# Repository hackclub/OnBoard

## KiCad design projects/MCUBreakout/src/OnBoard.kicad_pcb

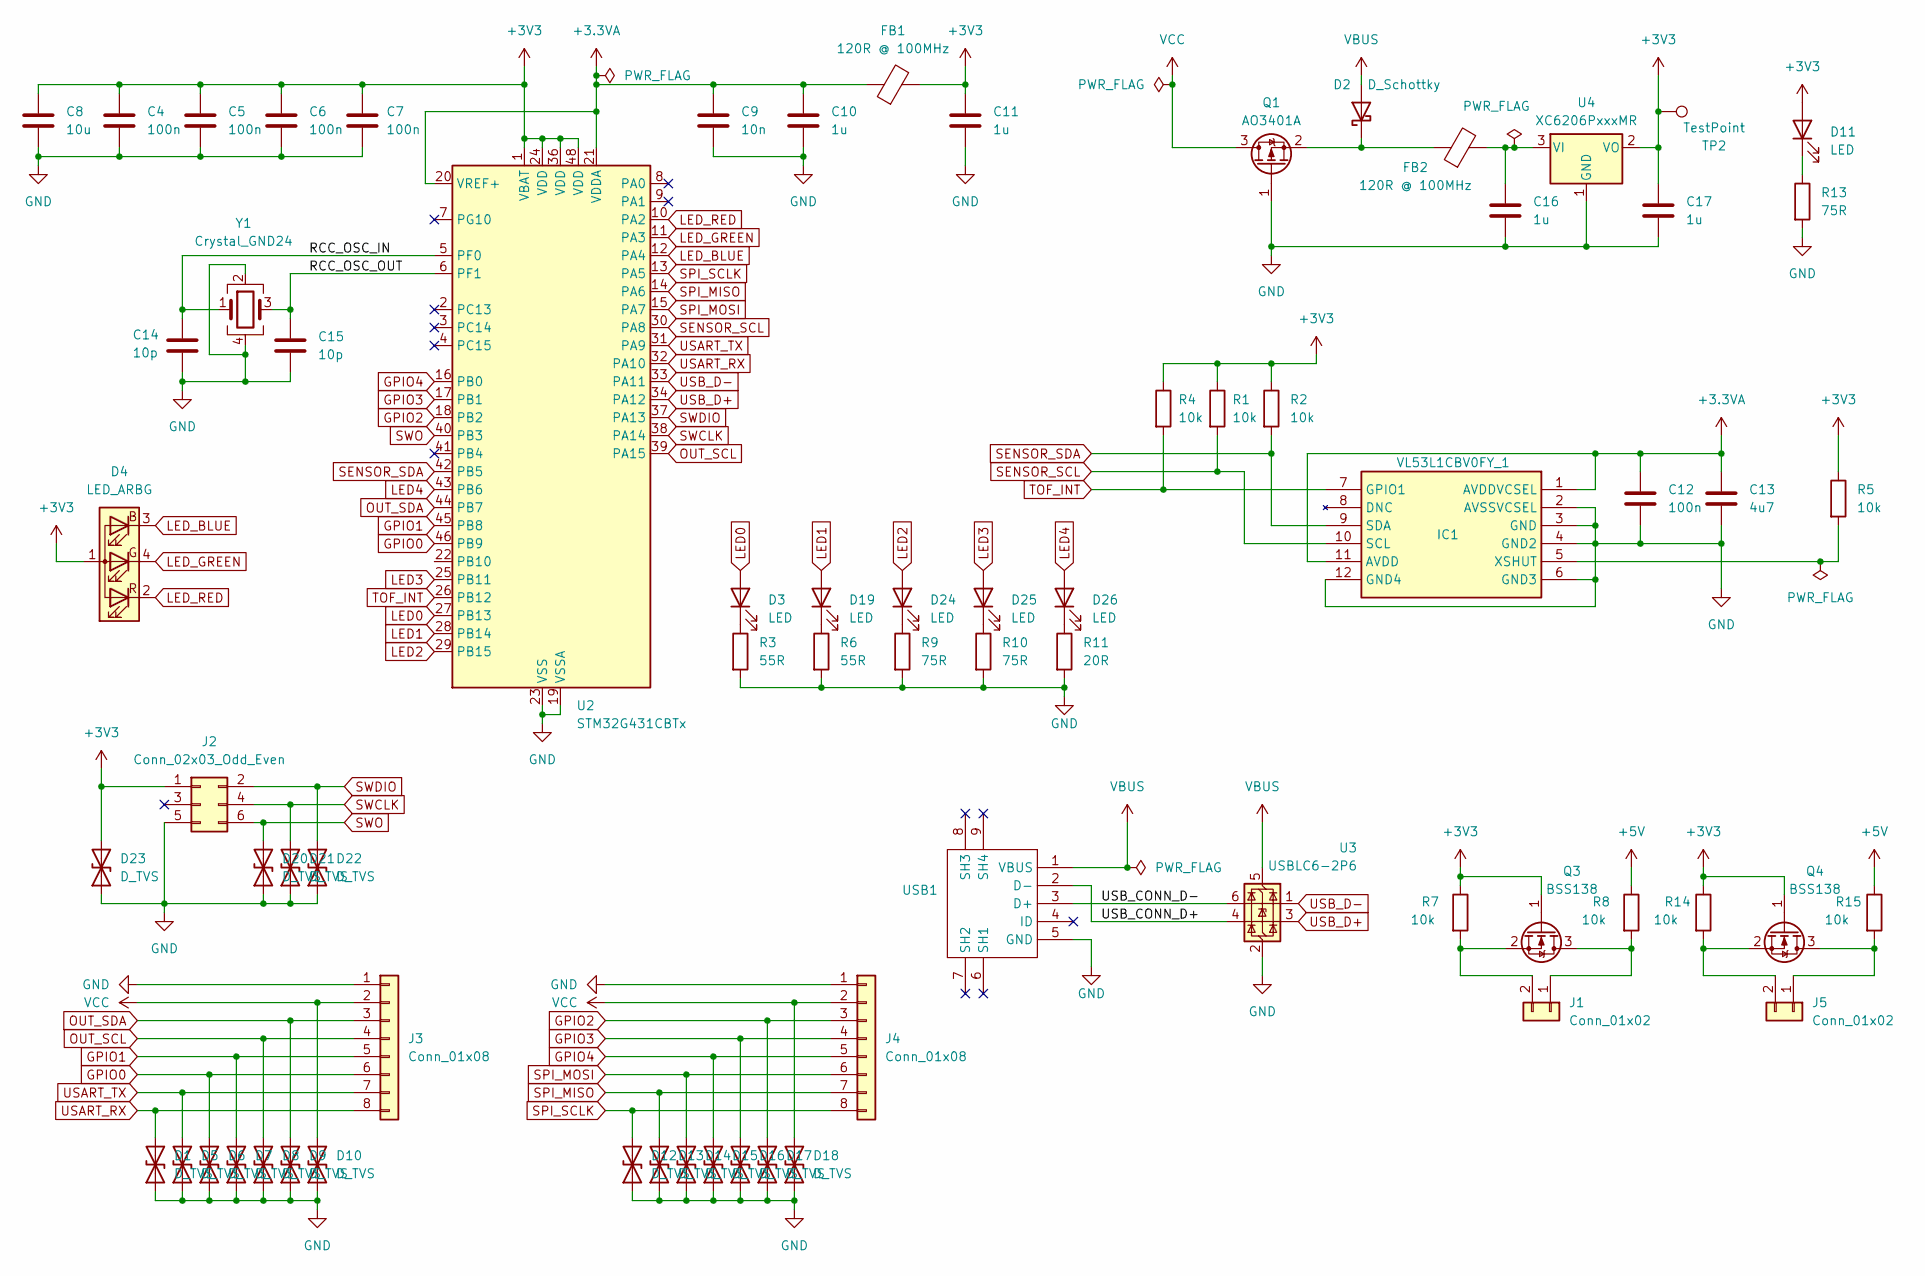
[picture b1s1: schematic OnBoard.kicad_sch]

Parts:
C4, C5, C6, C7, C12: 100n; C_0402_1005Metric
C8: 10u; C_0402_1005Metric
C9: 10n; C_0402_1005Metric
C10, C11, C16, C17: 1u; C_0402_1005Metric
C13: 4u7; C_0402_1005Metric
C14, C15: 10p; C_0402_1005Metric
D1, D5, D6, D7, D8, D9, D12, D13, D14, D15, D16, D17, D20, D21, D22, D23: D_TVS; TVS-3V3-DFN0603-2_L0.6-W0.3-BI
D2: D_Schottky; D_SOD-123
D3, D11, D19, D24, D25: LED; LED_0603_1608Metric
D4: LED_ARBG; HSMFC116
D10, D18: D_TVS; TVS-5V-DFN1006-2L-BI
D26: LED; LED_0805_2012Metric
FB1, FB2: 120R @ 100MHz; L_0603_1608Metric
IC1: VL53L1CBV0FY_1; VL53L1CBV0FY1; Manufacturer_Part_Number VL53L1CBV0FY/1; Mouser Part Number 511-VL53L1CBV0FY/1
J1, J5: Conn_01x02; PinHeader_1x02_P2.54mm_Vertical
J2: Conn_02x03_Odd_Even; Tag-Connect_TC2030-IDC-NL_2x03_P1.27mm_Vertical
J3, J4: Conn_01x08; PinHeader_1x08_P2.54mm_Vertical
Q1: AO3401A; SOT-23
Q3, Q4: BSS138; SOT-23
R1, R2, R4, R5, R7, R8, R14, R15: 10k; R_0402_1005Metric
R3, R6: 55R; R_0402_1005Metric
R9, R10, R13: 75R; R_0402_1005Metric
R11: 20R; R_0402_1005Metric
TP2: TestPoint; TestPoint_Pad_1.0x1.0mm
U2: STM32G431CBTx; LQFP-48_7x7mm_P0.5mm
U3: USBLC6-2P6; SOT-666
U4: XC6206PxxxMR; SOT-23-3
USB1: MICRO-USB-SMD_MICROXNJ; Manufacturer Part MicroXNJ; LCSC Part Name Micro-B 母 卧贴
Y1: Crystal_GND24; Crystal_SMD_3225-4Pin_3.2x2.5mm

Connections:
+3.3VA: C9.1, C10.1, C12.1, C13.1, FB1.1, IC1.1 (AVDDVCSEL), IC1.11 (AVDD), U2.20 (VREF+), U2.21 (VDDA)
+3V3: C4.1, C5.1, C6.1, C7.1, C8.1, C11.1, C17.1, D4.1 (A), D11.2 (A), D23.2 (A2), FB1.2, J2.1, Q3.1 (G), Q4.1 (G), R1.1, R2.1, R4.1, R5.1, R7.1, R14.1, TP2.1, U2.1 (VBAT), U2.24 (VDD), U2.36 (VDD), U2.48 (VDD), U4.2 (VO)
+5V: R8.1, R15.1
/RCC_OSC_IN: C14.1, U2.5 (PF0), Y1.1
/RCC_OSC_OUT: C15.1, U2.6 (PF1), Y1.3
/USB_CONN_D+: U3.4 (I/O2), USB1.2 (D-)
/USB_CONN_D-: U3.6 (I/O1), USB1.3 (D+)
GND: C4.2, C5.2, C6.2, C7.2, C8.2, C9.2, C10.2, C11.2, C12.2, C13.2, C14.2, C15.2, C16.2, C17.2, D1.1 (A1), D5.1 (A1), D6.1 (A1), D7.1 (A1), D8.1 (A1), D9.1 (A1), D10.1 (A1), D12.1 (A1), D13.1 (A1), D14.1 (A1), D15.1 (A1), D16.1 (A1), D17.1 (A1), D18.1 (A1), D20.1 (A1), D21.1 (A1), D22.1 (A1), D23.1 (A1), IC1.2 (AVSSVCSEL), IC1.3 (GND), IC1.4 (GND2), IC1.6 (GND3), IC1.12 (GND4), J2.5, J3.1, J4.1, Q1.1 (G), R3.2, R6.2, R9.2, R10.2, R11.2, R13.2, U2.19 (VSSA), U2.23 (VSS), U2.35 (VSS), U2.47 (VSS), U3.2 (GND), U4.1 (GND), USB1.5 (GND), Y1.2, Y1.4
GPIO0: D6.2 (A2), J3.6, U2.46 (PB9)
GPIO1: D7.2 (A2), J3.5, U2.45 (PB8)
GPIO2: D17.2 (A2), J4.3, U2.18 (PB2)
GPIO3: D16.2 (A2), J4.4, U2.17 (PB1)
GPIO4: D15.2 (A2), J4.5, U2.16 (PB0)
LED0: D3.2 (A), U2.27 (PB13)
LED1: D19.2 (A), U2.28 (PB14)
LED2: D24.2 (A), U2.29 (PB15)
LED3: D25.2 (A), U2.25 (PB11)
LED4: D26.2 (A), U2.43 (PB6)
LED_BLUE: D4.3 (BK), U2.12 (PA4)
LED_GREEN: D4.4 (GK), U2.11 (PA3)
LED_RED: D4.2 (RK), U2.10 (PA2)
unnamed: D2.1 (K), FB2.1, Q1.2 (S)
unnamed: D3.1 (K), R3.1
unnamed: D11.1 (K), R13.1
unnamed: D19.1 (K), R6.1
unnamed: D24.1 (K), R9.1
unnamed: D25.1 (K), R10.1
unnamed: D26.1 (K), R11.1
unnamed: IC1.5 (XSHUT), R5.2
unnamed: J1.1, Q3.3 (D), R8.2
unnamed: J1.2, Q3.2 (S), R7.2
unnamed: J5.1, Q4.3 (D), R15.2
unnamed: J5.2, Q4.2 (S), R14.2
unnamed: C16.1, FB2.2, U4.3 (VI)
OUT_SCL: D8.2 (A2), J3.4, U2.39 (PA15)
OUT_SDA: D9.2 (A2), J3.3, U2.44 (PB7)
SENSOR_SCL: IC1.10 (SCL), R1.2, U2.30 (PA8)
SENSOR_SDA: IC1.9 (SDA), R2.2, U2.42 (PB5)
SPI_MISO: D13.2 (A2), J4.7, U2.14 (PA6)
SPI_MOSI: D14.2 (A2), J4.6, U2.15 (PA7)
SPI_SCLK: D12.2 (A2), J4.8, U2.13 (PA5)
SWCLK: D21.2 (A2), J2.4, U2.38 (PA14)
SWDIO: D22.2 (A2), J2.2, U2.37 (PA13)
SWO: D20.2 (A2), J2.6, U2.40 (PB3)
TOF_INT: IC1.7 (GPIO1), R4.2, U2.26 (PB12)
USART_RX: D1.2 (A2), J3.8, U2.32 (PA10)
USART_TX: D5.2 (A2), J3.7, U2.31 (PA9)
USB_D+: U2.34 (PA12), U3.3 (I/O2)
USB_D-: U2.33 (PA11), U3.1 (I/O1)
VBUS: D2.2 (A), U3.5 (VBUS), USB1.1 (VBUS)
VCC: D10.2 (A2), D18.2 (A2), J3.2, J4.2, Q1.3 (D)

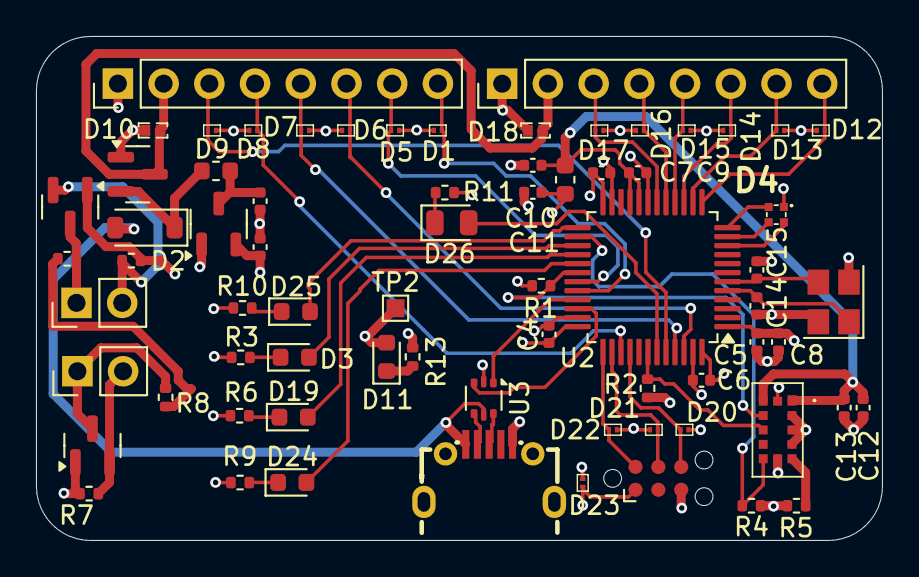
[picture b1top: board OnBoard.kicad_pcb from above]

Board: 4 copper layers, 47.0 x 28.0 mm, 71 parts (0 on the bottom side), 51 nets.

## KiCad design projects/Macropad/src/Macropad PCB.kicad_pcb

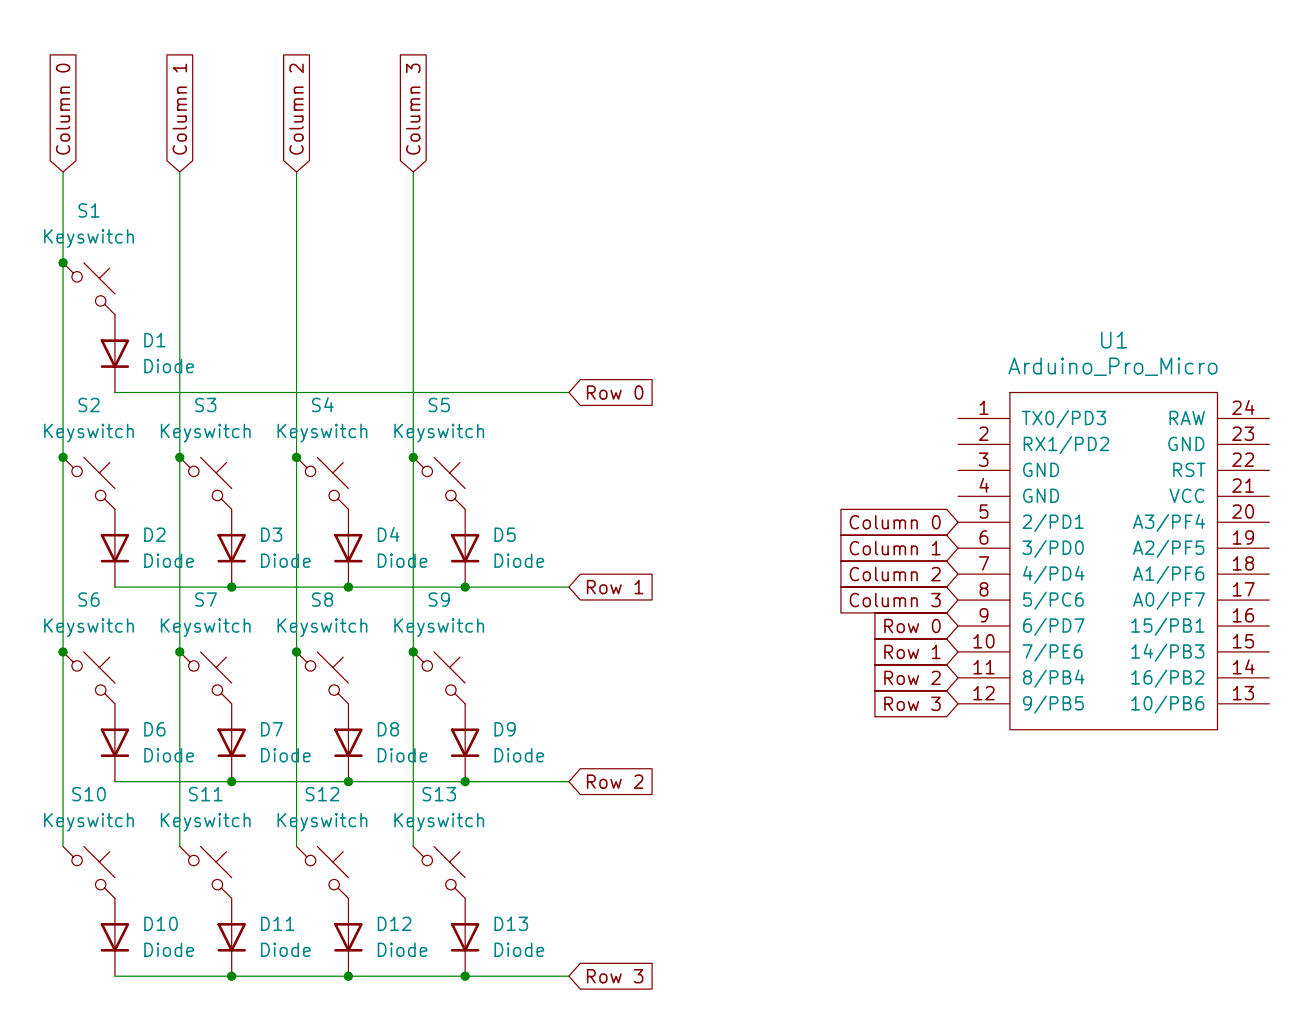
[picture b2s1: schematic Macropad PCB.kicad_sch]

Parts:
D1, D2, D3, D4, D5, D6, D7, D8, D9, D10, D11, D12, D13: Diode; Diode_DO-35
S1, S2, S3, S4, S5, S6, S7, S8, S9, S10, S11, S12, S13: Keyswitch; MX_PCB_1.00u
U1: Arduino_Pro_Micro

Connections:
Column 0: S1.1, S2.1, S6.1, S10.1, U1.5 (2/PD1)
Column 1: S3.1, S7.1, S11.1, U1.6 (3/PD0)
Column 2: S4.1, S8.1, S12.1, U1.7 (4/PD4)
Column 3: S5.1, S9.1, S13.1, U1.8 (5/PC6)
unnamed: D1.2 (A), S1.2
unnamed: D2.2 (A), S2.2
unnamed: D3.2 (A), S3.2
unnamed: D4.2 (A), S4.2
unnamed: D5.2 (A), S5.2
unnamed: D6.2 (A), S6.2
unnamed: D7.2 (A), S7.2
unnamed: D8.2 (A), S8.2
unnamed: D9.2 (A), S9.2
unnamed: D10.2 (A), S10.2
unnamed: D11.2 (A), S11.2
unnamed: D12.2 (A), S12.2
unnamed: D13.2 (A), S13.2
Row 0: D1.1 (K), U1.9 (6/PD7)
Row 1: D2.1 (K), D3.1 (K), D4.1 (K), D5.1 (K), U1.10 (7/PE6)
Row 2: D6.1 (K), D7.1 (K), D8.1 (K), D9.1 (K), U1.11 (8/PB4)
Row 3: D10.1 (K), D11.1 (K), D12.1 (K), D13.1 (K), U1.12 (9/PB5)

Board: 2 copper layers, 27 parts (0 on the bottom side), 21 nets, no tracks yet.

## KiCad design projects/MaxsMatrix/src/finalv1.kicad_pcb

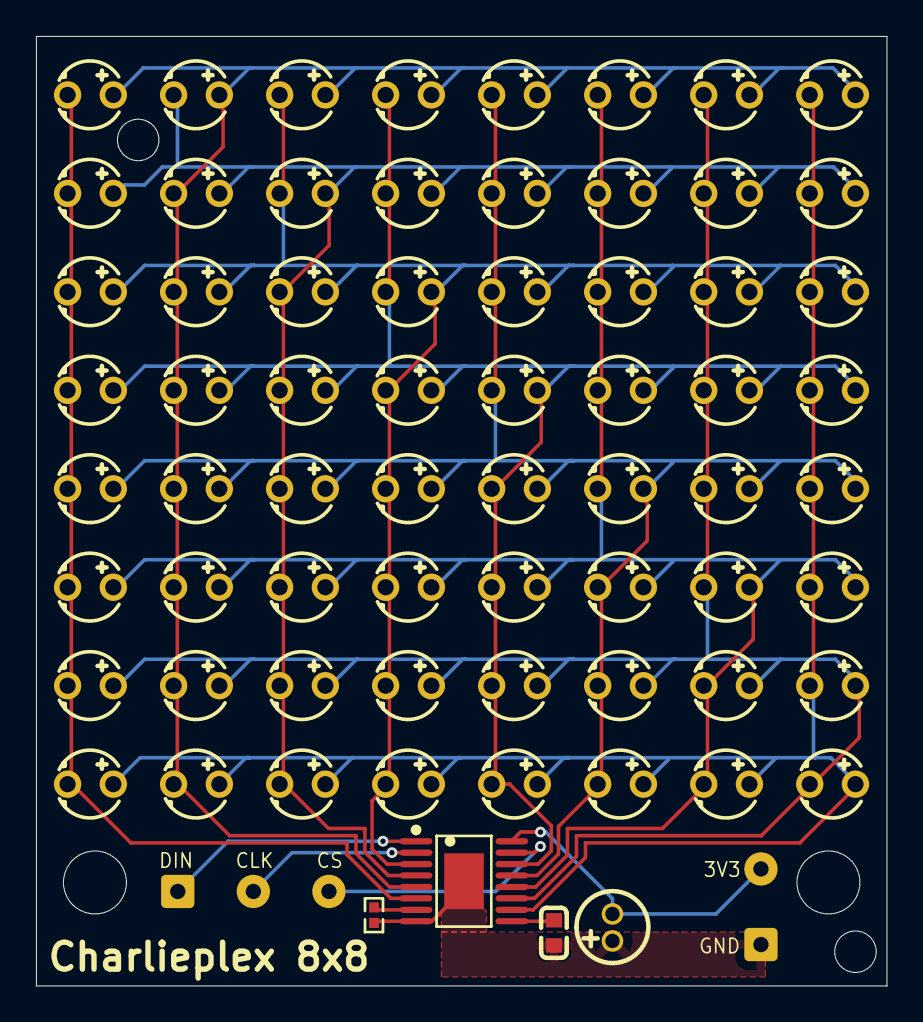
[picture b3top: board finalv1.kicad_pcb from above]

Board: 2 copper layers, 47.2 x 52.8 mm, 70 parts (0 on the bottom side), 16 nets.

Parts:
C2: 100nF; CAP-TH_BD4.0-P1.50-D0.8-FD
C3: 27pF; C0603
D1, D2, D3, D4, D5, D6, D7, D8, D9, D10, D11, D12, D13, D14, D15, D16, D17, D18, D19, D20, D21, D22, D23, D24, D25, D26, D27, D28, D29, D30, D31, D32, D33, D34, D35, D36, D37, D38, D39, D40, D41, D42, D43, D44, D45, D46, D47, D48, D49, D50, D51, D52, D53, D54, D55, D56, D57, D58, D59, D60, D61, D62, D63, D64: LED; LED-TH_BD3.8-P2.54-RD
J1: Power; SolderWire-0.25sqmm_1x02_P4.2mm_D0.65mm_OD1.7mm
J2: SPI; SolderWire-0.25sqmm_1x03_P4.2mm_D0.65mm_OD1.7mm
R1: 56kΩ; R0402
U1: MAX6951CEE_T; QSOP-16_L4.9-W3.9-P0.64-LS6.0-BL-EP-1

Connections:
+3.3V: C2.2, J1.2, U1.16 (V+)
/CA1: D1.1 (K), D2.1 (K), D3.1 (K), D4.1 (K), D5.1 (K), D6.1 (K), D7.1 (K), D8.1 (K), U1.6 (DIG0/SEG0)
/CA2: D1.2 (A), D9.2 (A), D10.1 (K), D11.1 (K), D12.1 (K), D13.1 (K), D14.1 (K), D15.1 (K), D16.1 (K), D17.2 (A), D25.2 (A), D33.2 (A), D41.2 (A), D49.2 (A), D57.2 (A), U1.5 (DIG1/SEG1)
/CA3: D2.2 (A), D9.1 (K), D10.2 (A), D18.2 (A), D19.1 (K), D20.1 (K), D21.1 (K), D22.1 (K), D23.1 (K), D24.1 (K), D26.2 (A), D34.2 (A), D42.2 (A), D50.2 (A), D58.2 (A), U1.4 (DIG2/SEG2)
/CA4: D3.2 (A), D11.2 (A), D17.1 (K), D18.1 (K), D19.2 (A), D27.2 (A), D28.1 (K), D29.1 (K), D30.1 (K), D31.1 (K), D32.1 (K), D35.2 (A), D43.2 (A), D51.2 (A), D59.2 (A), U1.3 (DIG3/SEG3)
/CA5: D4.2 (A), D12.2 (A), D20.2 (A), D25.1 (K), D26.1 (K), D27.1 (K), D28.2 (A), D36.2 (A), D37.1 (K), D38.1 (K), D39.1 (K), D40.1 (K), D44.2 (A), D52.2 (A), D60.2 (A), U1.14 (DIG4/SEG4)
/CA6: D5.2 (A), D13.2 (A), D21.2 (A), D29.2 (A), D33.1 (K), D34.1 (K), D35.1 (K), D36.1 (K), D37.2 (A), D45.2 (A), D46.1 (K), D47.1 (K), D48.1 (K), D53.2 (A), D61.2 (A), U1.13 (DIG5/SEG5)
/CA7: D6.2 (A), D14.2 (A), D22.2 (A), D30.2 (A), D38.2 (A), D41.1 (K), D42.1 (K), D43.1 (K), D44.1 (K), D45.1 (K), D46.2 (A), D54.2 (A), D55.1 (K), D56.1 (K), D62.2 (A), U1.12 (DIG6/SEG6)
/CA8: D7.2 (A), D15.2 (A), D23.2 (A), D31.2 (A), D39.2 (A), D47.2 (A), D49.1 (K), D50.1 (K), D51.1 (K), D52.1 (K), D53.1 (K), D54.1 (K), D55.2 (A), D63.2 (A), D64.1 (K), U1.11 (DIG7/SEG7)
/CA9: D8.2 (A), D16.2 (A), D24.2 (A), D32.2 (A), D40.2 (A), D48.2 (A), D56.2 (A), D57.1 (K), D58.1 (K), D59.1 (K), D60.1 (K), D61.1 (K), D62.1 (K), D63.1 (K), D64.2 (A), U1.10 (SEG8)
GND: C2.1, C3.2, J1.1, R1.2, U1.8 (GND), U1.17 (EXP)
unnamed: J2.1, U1.1 (DIN)
unnamed: J2.2, U1.2 (CLK)
unnamed: J2.3, U1.15 (~CS)
unnamed: R1.1, U1.7 (ISET)
unnamed: C3.1, U1.9 (OSC)

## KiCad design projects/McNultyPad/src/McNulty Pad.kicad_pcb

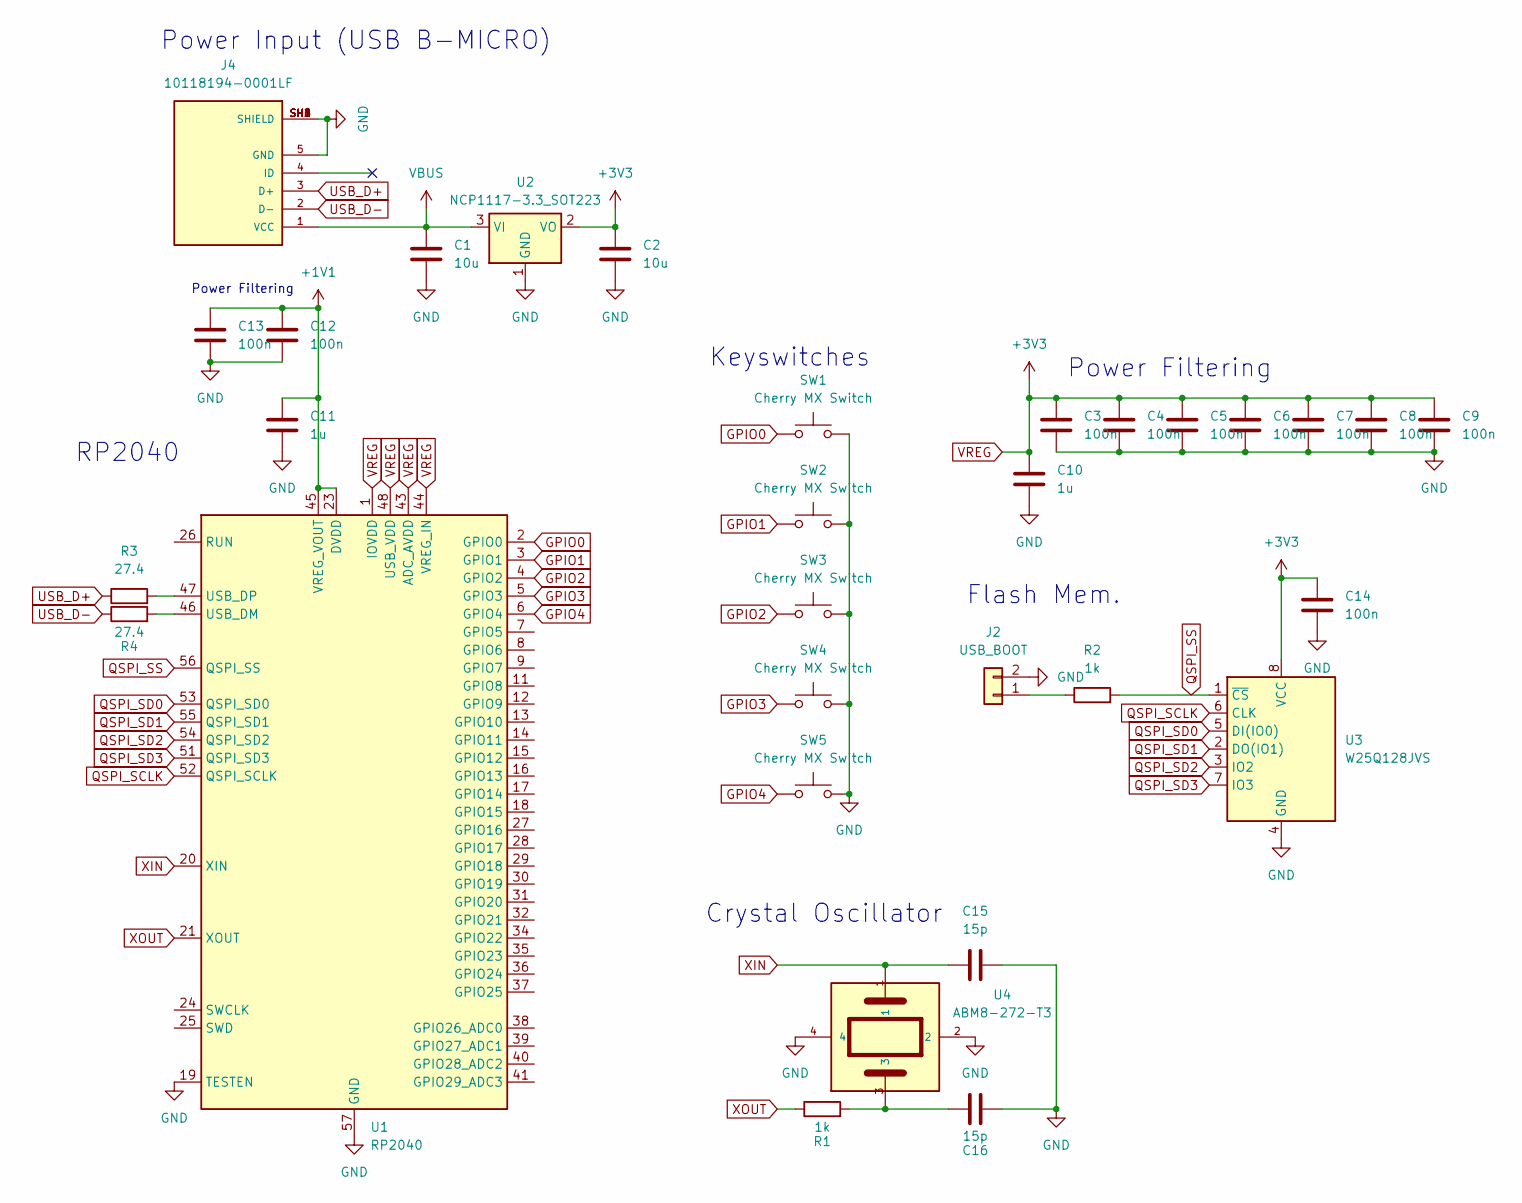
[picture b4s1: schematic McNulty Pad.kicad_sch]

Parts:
C1, C2: 10u; C_0402_1005Metric
C3, C4, C5, C6, C7, C8, C9, C12, C13, C14: 100n; C_0603_1608Metric
C10, C11: 1u; C_0402_1005Metric
C15, C16: 15p; C_0402_1005Metric
J2: USB_BOOT; PinHeader_1x02_P2.54mm_Vertical
J4: 10118194-0001LF; AMPHENOL_10118194-0001LF; PARTREV D
R1, R2: 1k; R_0603_1608Metric
R3, R4: 27.4; R_0603_1608Metric
SW1, SW2, SW3, SW4, SW5: Cherry MX Switch; SW_Cherry_MX_1.00u_PCB
U1: RP2040; QFN-56-1EP_7x7mm_P0.4mm_EP3.2x3.2mm
U2: NCP1117-3.3_SOT223; SOT-223-3_TabPin2
U3: W25Q128JVS; SOIC-8_5.23x5.23mm_P1.27mm
U4: ABM8-272-T3

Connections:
+1V1: C11.2, C12.1, C13.1, U1.23 (DVDD), U1.45 (VREG_VOUT), U1.50 (DVDD)
GND: C1.2, C2.2, C3.2, C4.2, C5.2, C6.2, C7.2, C8.2, C9.2, C10.2, C11.1, C12.2, C13.2, C14.2, C15.2, C16.1, J2.2, J4.5 (GND), J4.SH1 (SHIELD), J4.SH2 (SHIELD), J4.SH3 (SHIELD), J4.SH4 (SHIELD), J4.SH5 (SHIELD), J4.SH6 (SHIELD), SW1.2, SW2.2, SW3.2, SW4.2, SW5.2, U1.19 (TESTEN), U1.57 (GND), U2.1 (GND), U3.4 (GND), U4.2, U4.4
GPIO0: SW1.1, U1.2 (GPIO0)
GPIO1: SW2.1, U1.3 (GPIO1)
GPIO2: SW3.1, U1.4 (GPIO2)
GPIO3: SW4.1, U1.5 (GPIO3)
GPIO4: SW5.1, U1.6 (GPIO4)
unnamed: C16.2, R1.2, U4.3
unnamed: J2.1, R2.1
unnamed: R4.2, U1.46 (USB_DM)
unnamed: R3.2, U1.47 (USB_DP)
QSPI_SCLK: U1.52 (QSPI_SCLK), U3.6 (CLK)
QSPI_SD0: U1.53 (QSPI_SD0), U3.5 (DI(IO0))
QSPI_SD1: U1.55 (QSPI_SD1), U3.2 (DO(IO1))
QSPI_SD2: U1.54 (QSPI_SD2), U3.3 (IO2)
QSPI_SD3: U1.51 (QSPI_SD3), U3.7 (IO3)
QSPI_SS: R2.2, U1.56 (QSPI_SS), U3.1 (~CS)
USB_D+: J4.3 (D+), R3.1
USB_D-: J4.2 (D-), R4.1
VBUS: C1.1, J4.1 (VCC), U2.3 (VI)
VREG: C2.1, C3.1, C4.1, C5.1, C6.1, C7.1, C8.1, C9.1, C10.1, C14.1, U1.1 (IOVDD), U1.10 (IOVDD), U1.22 (IOVDD), U1.33 (IOVDD), U1.42 (IOVDD), U1.43 (ADC_AVDD), U1.44 (VREG_IN), U1.48 (USB_VDD), U1.49 (IOVDD), U2.2 (VO), U3.8 (VCC)
XIN: C15.1, U1.20 (XIN), U4.1
XOUT: R1.1, U1.21 (XOUT)

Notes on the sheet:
Power Filtering
Crystal Oscillator
RP2040
Flash Mem.
Keyswitches
Power Input (USB B-MICRO)
Power Filtering

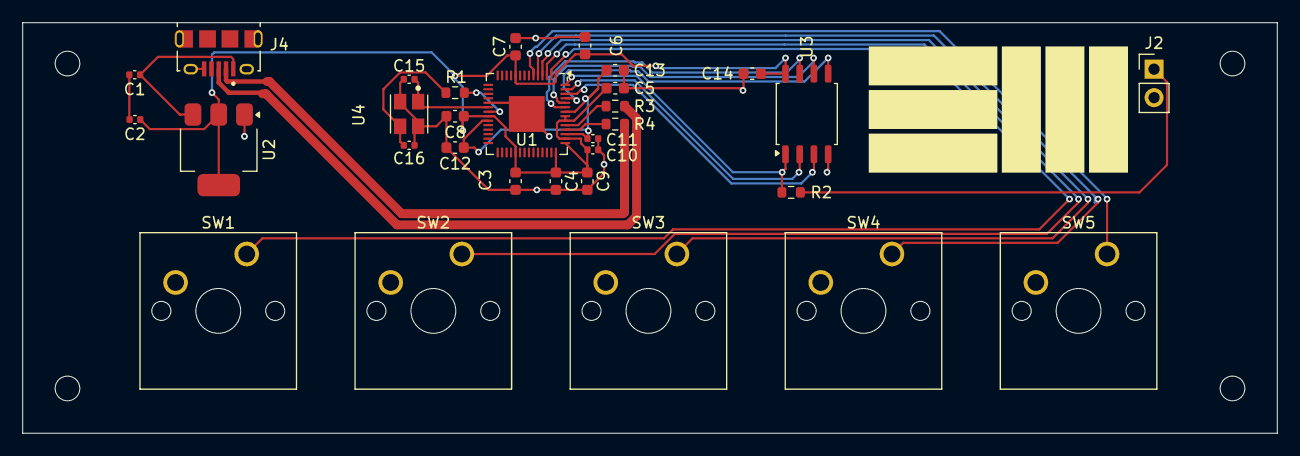
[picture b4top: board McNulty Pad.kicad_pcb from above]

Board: 2 copper layers, 112.0 x 36.6 mm, 31 parts (0 on the bottom side), 23 nets.

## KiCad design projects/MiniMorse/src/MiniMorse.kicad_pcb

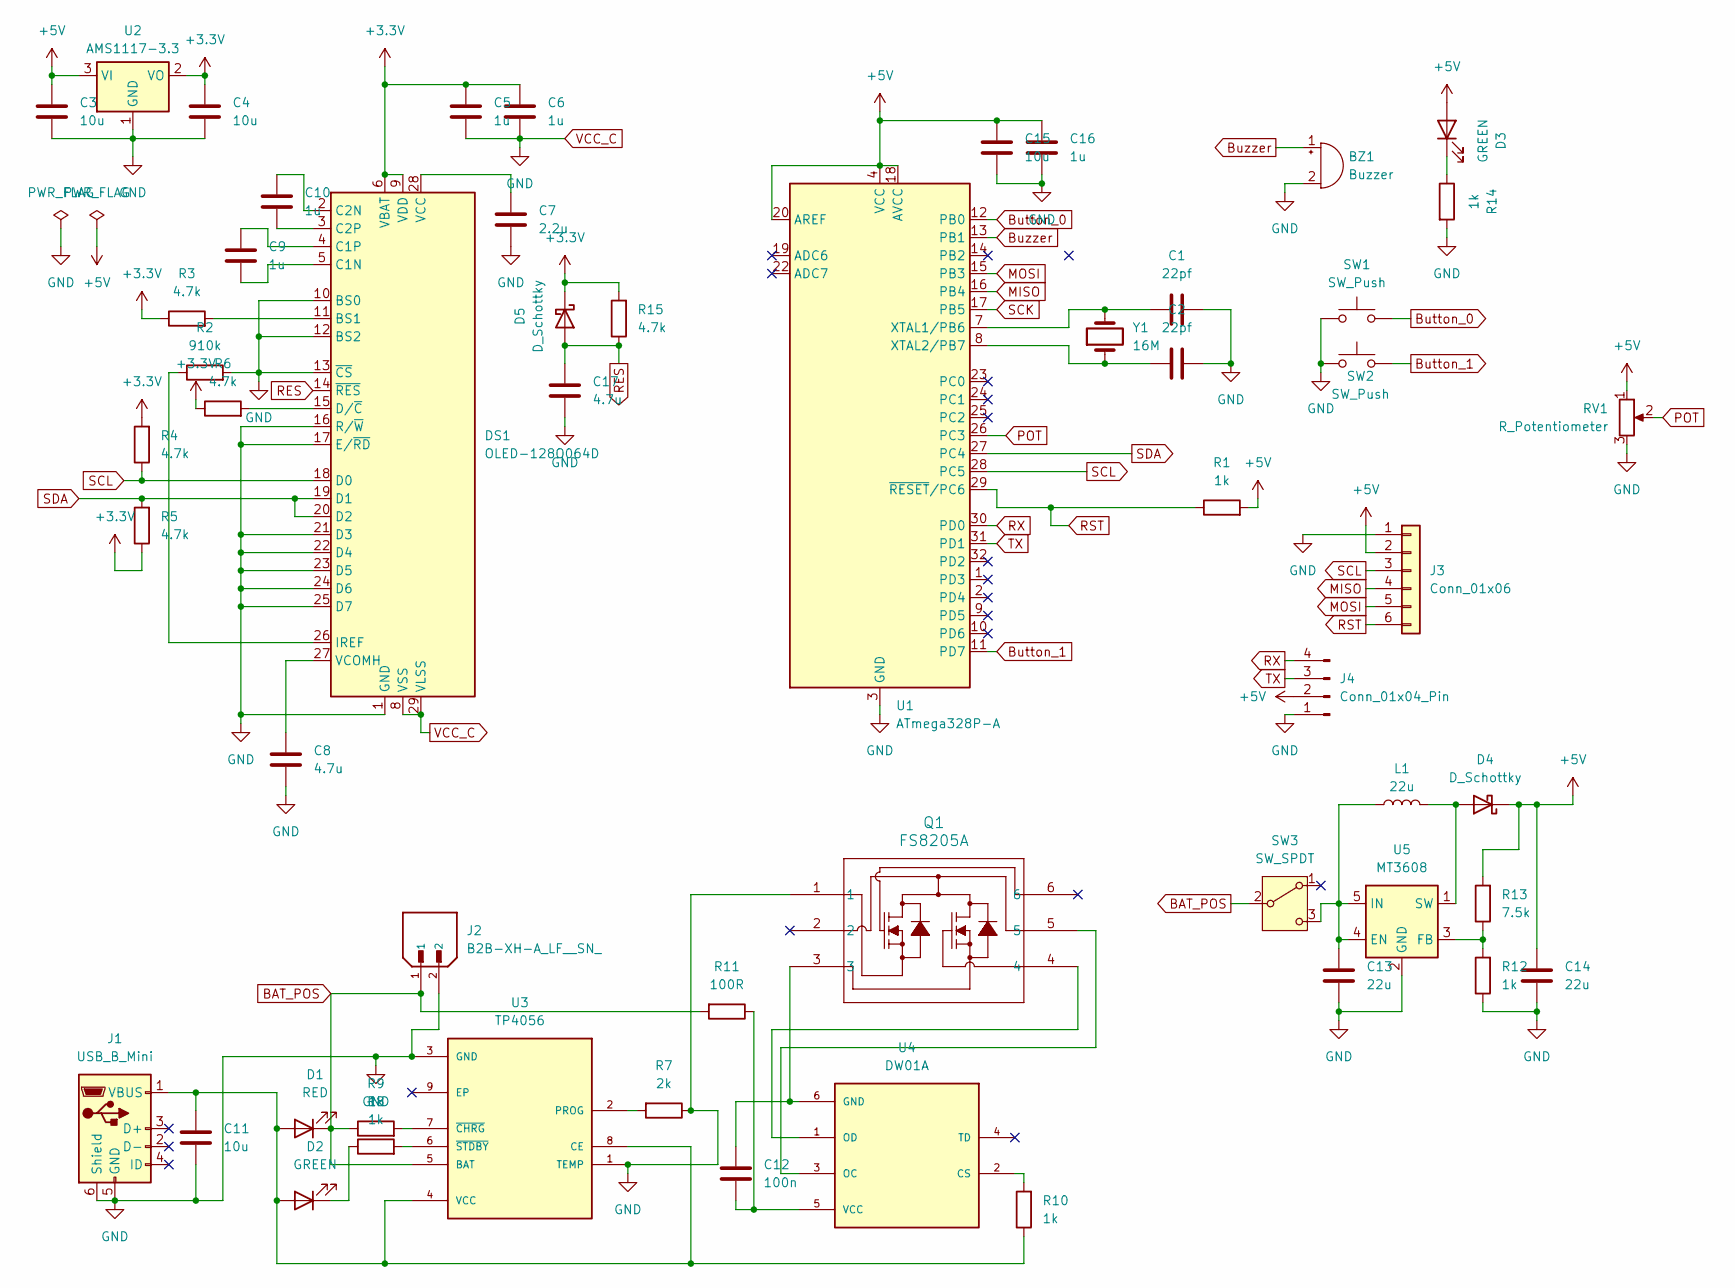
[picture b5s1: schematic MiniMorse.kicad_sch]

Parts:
BZ1: Buzzer; Buzzer_12x9.5RM7.6
C1, C2: 22pf; C_0805_2012Metric_Pad1.18x1.45mm_HandSolder
C3, C4, C11, C15: 10u; C_0805_2012Metric_Pad1.18x1.45mm_HandSolder
C5, C6, C9, C10, C16: 1u; C_0805_2012Metric_Pad1.18x1.45mm_HandSolder
C7: 2.2u; C_0805_2012Metric_Pad1.18x1.45mm_HandSolder
C8, C17: 4.7u; C_0805_2012Metric_Pad1.18x1.45mm_HandSolder
C12: 100n; C_0805_2012Metric_Pad1.18x1.45mm_HandSolder
C13, C14: 22u; C_0805_2012Metric_Pad1.18x1.45mm_HandSolder
D1: RED; LED_0805_2012Metric_Pad1.15x1.40mm_HandSolder
D2, D3: GREEN; LED_0805_2012Metric_Pad1.15x1.40mm_HandSolder
D4, D5: D_Schottky; D_SMC_Handsoldering
DS1: OLED-128O064D
J1: USB_B_Mini; USB_Mini-B_Lumberg_2486_01_Horizontal
J2: B2B-XH-A_LF__SN_; JST_B2B-XH-A_LF__SN_; PARTREV N/A
J3: Conn_01x06; PinHeader_1x06_P2.54mm_Vertical
J4: Conn_01x04_Pin; PinSocket_1x04_P2.54mm_Vertical
L1: 22u; L_Bourns_SRP7028A_7.3x6.6mm
Q1: FS8205A; SOT-23-6L_TCP
R1, R8, R9, R10, R12, R14: 1k; R_0805_2012Metric_Pad1.20x1.40mm_HandSolder
R2: 910k; R_0805_2012Metric_Pad1.20x1.40mm_HandSolder
R3, R4, R5, R6, R15: 4.7k; R_0805_2012Metric_Pad1.20x1.40mm_HandSolder
R7: 2k; R_0805_2012Metric_Pad1.20x1.40mm_HandSolder
R11: 100R; R_0805_2012Metric_Pad1.20x1.40mm_HandSolder
R13: 7.5k; R_0805_2012Metric_Pad1.20x1.40mm_HandSolder
RV1: R_Potentiometer; Potentiometer_Alps_RK09K_Single_Vertical
SW1, SW2: SW_Push; SW_Push_1P1T_NO_6x6mm_H9.5mm
SW3: SW_SPDT; SS-12D10L5
U1: ATmega328P-A; TQFP-32_7x7mm_P0.8mm
U2: AMS1117-3.3; SOT-223-3_TabPin2
U3: TP4056; SOP127P600X175-9N
U4: DW01A; SOT95P280X145-6N; PARTREV 1.8
U5: MT3608; SOT-23-6
Y1: 16M; Crystal_SMD_3225-4Pin_3.2x2.5mm_HandSoldering

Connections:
+3.3V: C4.2, C5.2, C6.2, D5.1 (K), DS1.6 (VBAT), DS1.9 (VDD), R3.1, R4.2, R5.1, R6.1, R15.2, U2.2 (VO)
+5V: C3.2, C14.2, C15.2, C16.2, D3.2 (A), D4.1 (K), J3.2, J4.2, R1.2, R13.2, RV1.1, U1.4 (VCC), U1.6 (VCC), U1.18 (AVCC), U1.20 (AREF), U2.3 (VI)
BAT_POS: D1.1 (K), J2.1, R9.1, R11.2, SW3.2 (B), U3.5 (BAT)
Button_0: SW1.2, U1.12 (PB0)
Button_1: SW2.2, U1.11 (PD7)
Buzzer: BZ1.1 (+), U1.13 (PB1)
MISO: J3.4, U1.16 (PB4)
MOSI: J3.5, U1.15 (PB3)
unnamed: C11.2, D1.2 (A), D2.2 (A), J1.1 (VBUS), R10.1, U3.4 (VCC), U3.8 (CE)
unnamed: D2.1 (K), R8.1
unnamed: D3.1 (K), R14.1
unnamed: D4.2 (A), L1.2, U5.1 (SW)
unnamed: DS1.11 (BS1), R3.2
unnamed: C9.1, DS1.5 (C1N)
unnamed: C9.2, DS1.4 (C1P)
unnamed: C10.2, DS1.2 (C2N)
unnamed: C10.1, DS1.3 (C2P)
unnamed: DS1.15 (D/~C), R6.2
unnamed: DS1.26 (IREF), R2.1
unnamed: C7.1, DS1.28 (VCC)
unnamed: C8.1, DS1.27 (VCOMH)
unnamed: C13.2, L1.1, SW3.3 (C), U5.4 (EN), U5.5 (IN)
unnamed: C1.1, U1.7 (XTAL1/PB6), Y1.2
unnamed: C2.1, U1.8 (XTAL2/PB7), Y1.1
unnamed: R7.2, U3.2 (PROG)
unnamed: R9.2, U3.7 (~CHRG)
unnamed: R8.2, U3.6 (~STDBY)
unnamed: R10.2, U4.2 (CS)
unnamed: C12.2, Q1.3, U4.6 (GND)
unnamed: Q1.5, U4.3 (OC)
unnamed: Q1.4, U4.1 (OD)
unnamed: C12.1, R11.1, U4.5 (VCC)
unnamed: R12.2, R13.1, U5.3 (FB)
POT: RV1.2, U1.26 (PC3)
RES: C17.1, D5.2 (A), DS1.14 (~RES), R15.1
RST: J3.6, R1.1, U1.29 (~RESET/PC6)
RX: J4.4, U1.30 (PD0)
SCK: U1.17 (PB5)
SCL: DS1.18 (D0), J3.3, R4.1, U1.28 (PC5)
SDA: DS1.19 (D1), DS1.20 (D2), R5.2, U1.27 (PC4)
TX: J4.3, U1.31 (PD1)
VCC_C: BZ1.2 (-), C1.2, C2.2, C3.1, C4.1, C5.1, C6.1, C7.2, C8.2, C11.1, C13.1, C14.1, C15.1, C16.1, C17.2, DS1.1 (GND), DS1.8 (VSS), DS1.10 (BS0), DS1.12 (BS2), DS1.13 (~CS), DS1.16 (R/~W), DS1.17 (E/~RD), DS1.21 (D3), DS1.22 (D4), DS1.23 (D5), DS1.24 (D6), DS1.25 (D7), DS1.29 (VLSS), DS1.30 (GND), J1.5 (GND), J1.6 (Shield), J2.2, J3.1, J4.1, Q1.1, R2.2, R7.1, R12.1, R14.2, RV1.3, SW1.1, SW2.1, U1.3 (GND), U1.5 (GND), U1.21 (GND), U2.1 (GND), U3.1 (TEMP), U3.3 (GND), U5.2 (GND)

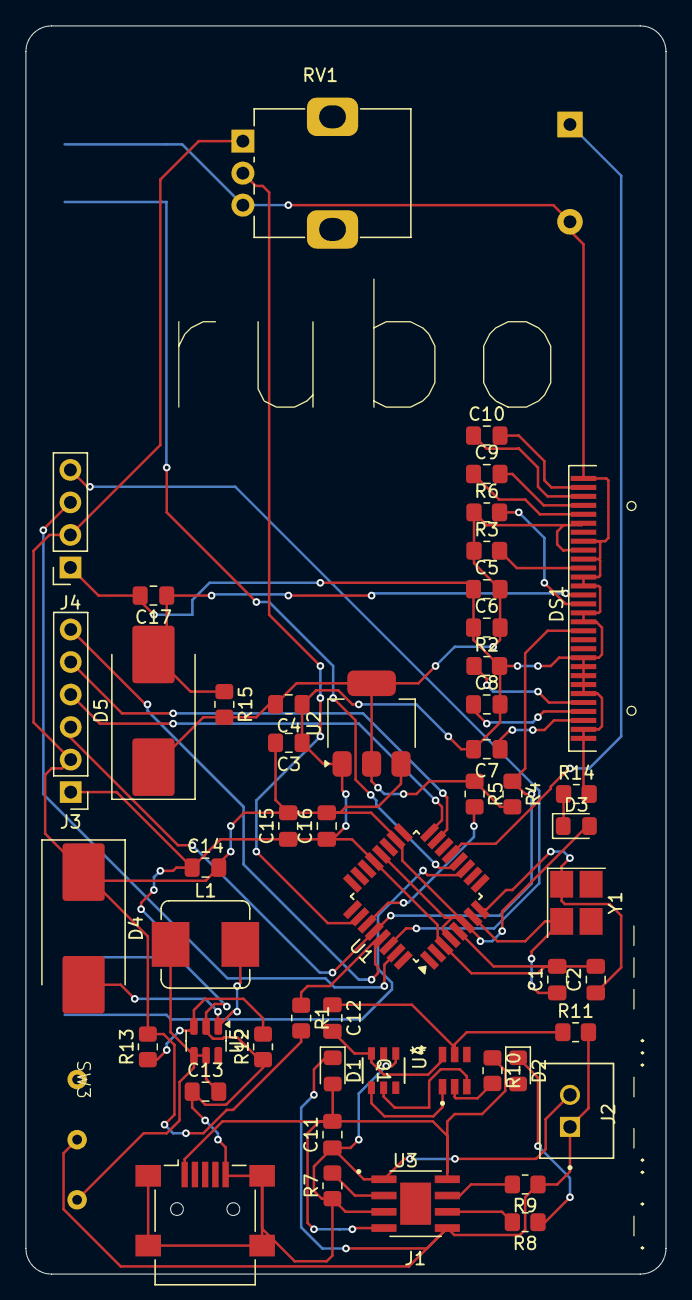
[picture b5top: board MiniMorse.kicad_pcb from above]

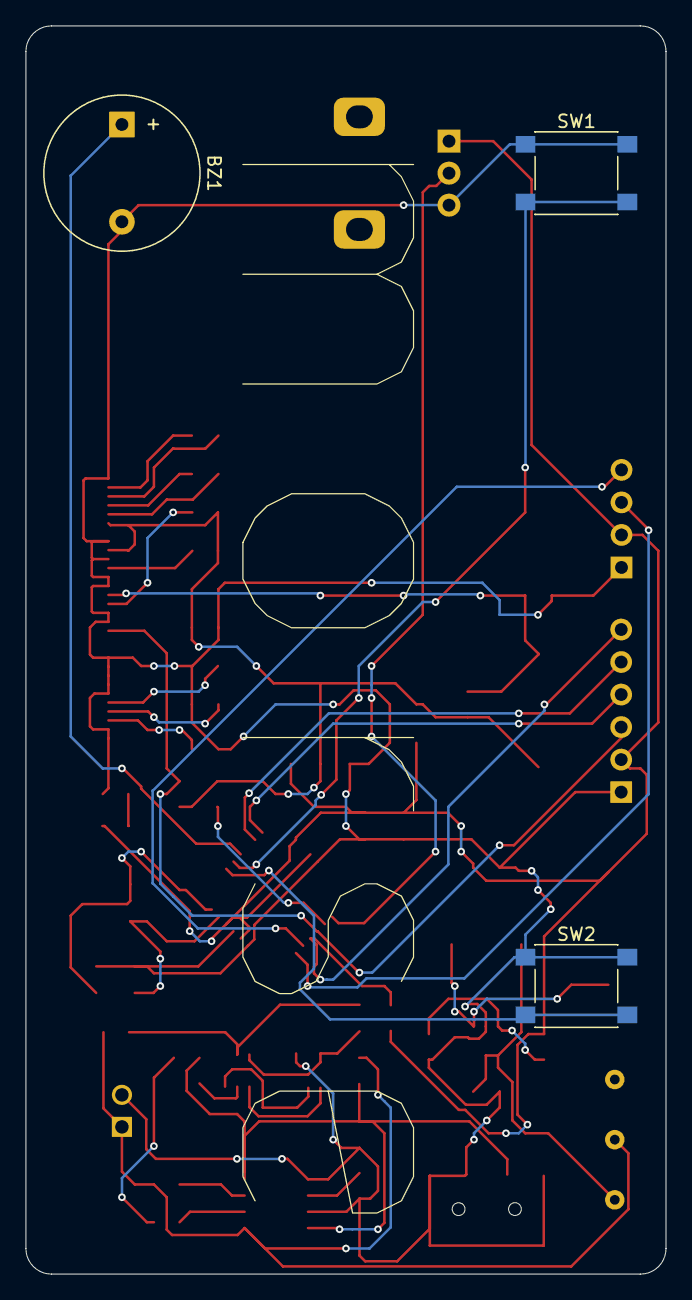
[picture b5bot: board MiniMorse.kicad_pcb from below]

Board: 2 copper layers, 50.0 x 97.5 mm, 55 parts (3 on the bottom side), 41 nets.

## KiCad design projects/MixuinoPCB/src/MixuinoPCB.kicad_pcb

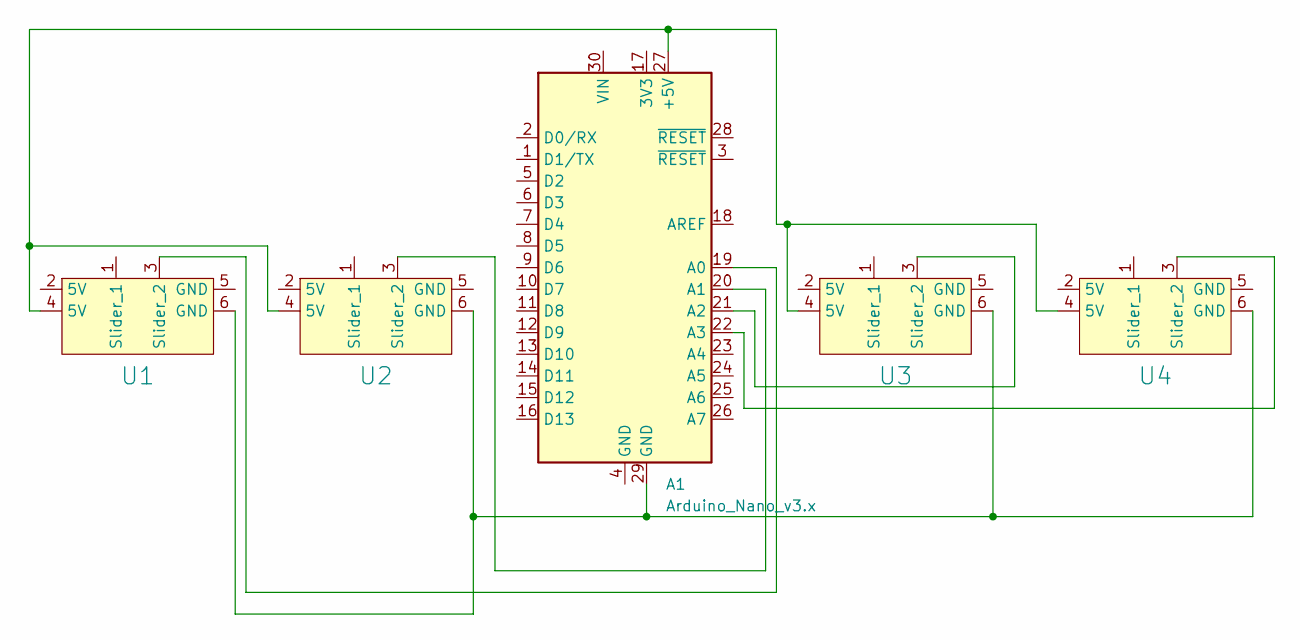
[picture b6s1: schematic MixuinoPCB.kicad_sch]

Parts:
A1: Arduino_Nano_v3.x; Arduino_Nano
U1, U2, U3, U4: Slide Potentiometer - B103

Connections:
unnamed: A1.27 (+5V), U1.4 (5V), U2.4 (5V), U3.4 (5V), U4.4 (5V)
unnamed: A1.19 (A0), U1.3 (Slider_2)
unnamed: A1.20 (A1), U2.3 (Slider_2)
unnamed: A1.21 (A2), U3.3 (Slider_2)
unnamed: A1.22 (A3), U4.3 (Slider_2)
unnamed: A1.29 (GND), U1.6 (GND), U2.6 (GND), U3.6 (GND), U4.6 (GND)

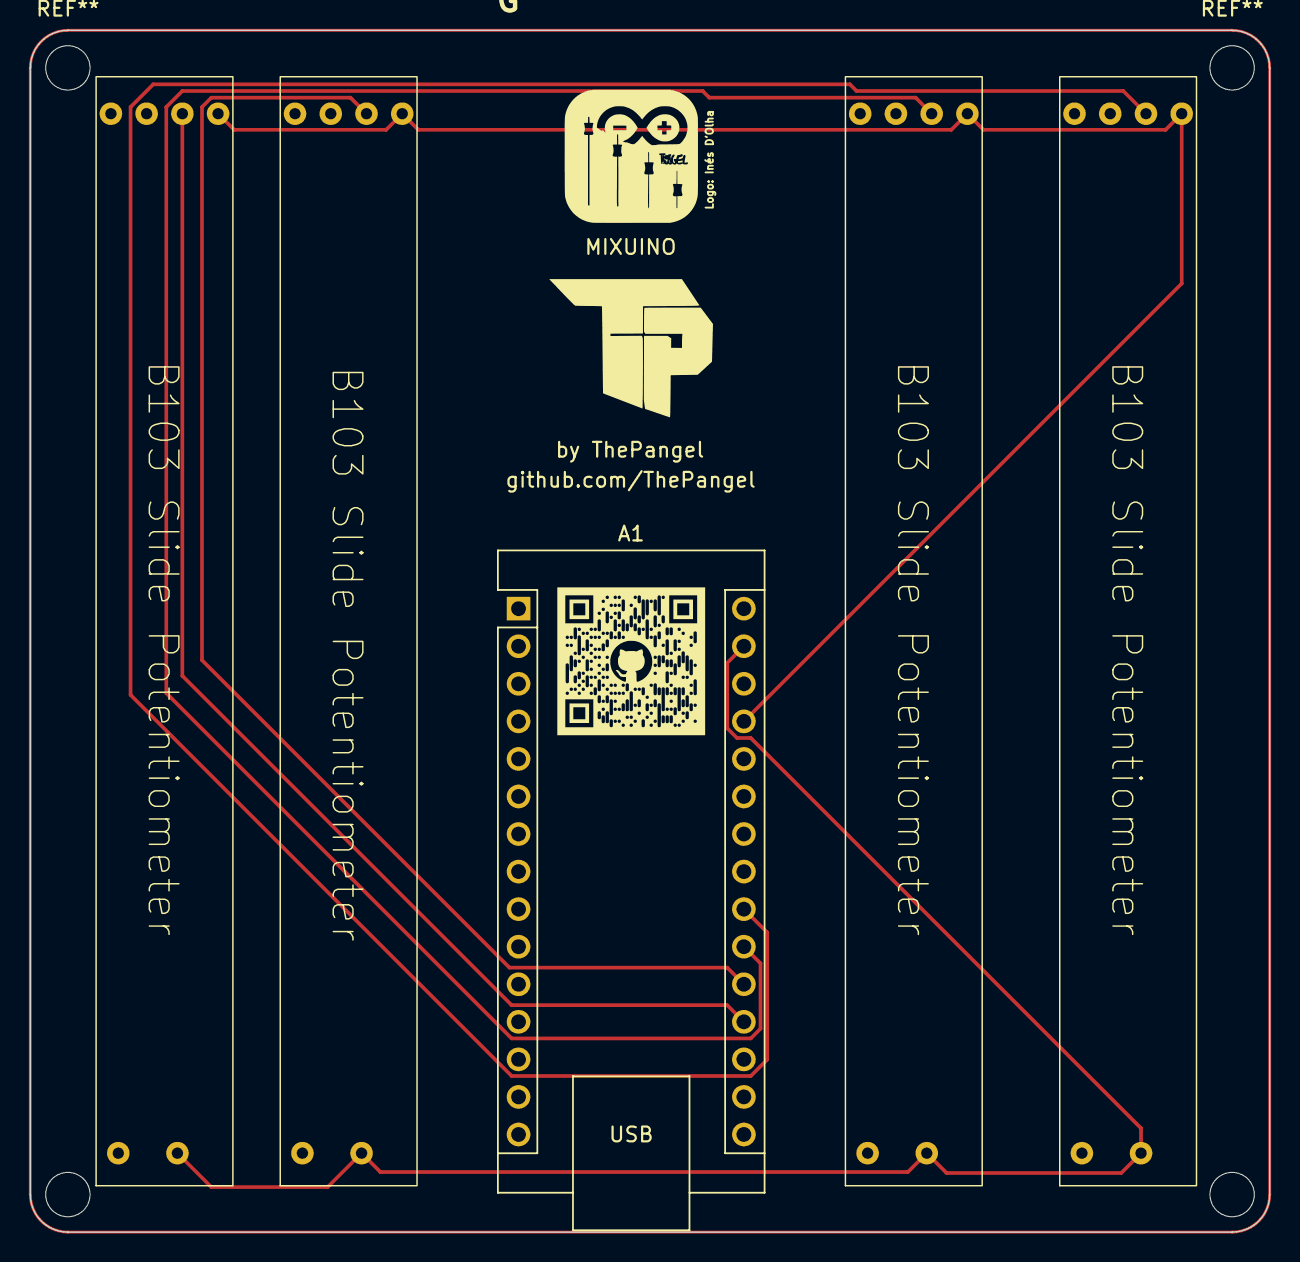
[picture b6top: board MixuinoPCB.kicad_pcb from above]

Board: 2 copper layers, 83.8 x 81.3 mm, 6 parts (0 on the bottom side), 6 nets.

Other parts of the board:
REF: LOGO
